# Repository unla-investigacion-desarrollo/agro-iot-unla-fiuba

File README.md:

# agro-iot-unla-fiuba

## Pasos necesarios para finalizar el proceso de subida.
1- Primero, para levantar el server de MQTT leer el readme dentro de /moquitto-docker
2- Luego, para levantar la capa lógica leer el readme dentro de /iot-src

## Nombre de aplicación que debe utilizarse.
sg.unla.edu.ar/iothuertas

## Persona a contactar como responsable de la aplicación.
Gustavo Hernan Siciliano (gussiciliano@gmail.com)

## Tiempo de vida de la aplicación en el servidor.
Todo 2024 (re evaluar en 2025)

## Extras (no necesarios para deployar en servidor):
a- Para cargar la placa con la configuración correcta del server MQTT leer el reame de /agroecologia-iot-dispositivo
b- Documentación de la placa:
https://drive.google.com/file/d/1S4R7Kyz0lglkcFME0CLmTT9d_WD0e9yo

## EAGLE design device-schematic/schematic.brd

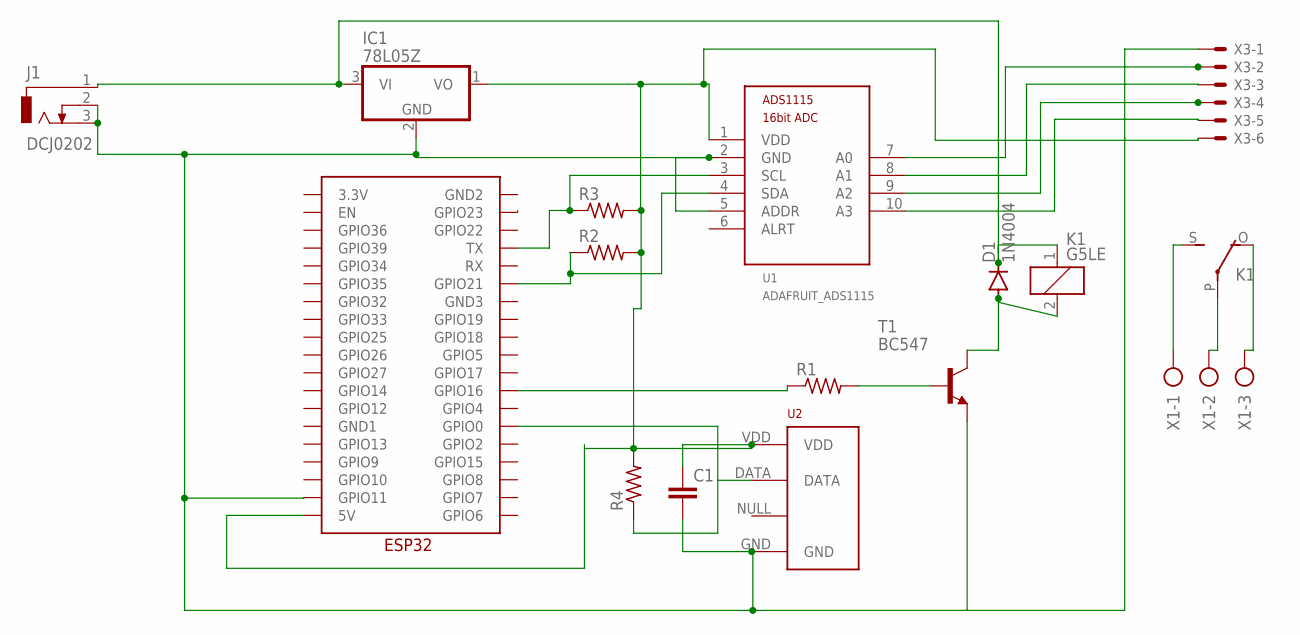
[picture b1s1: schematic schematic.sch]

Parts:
C1: C-EU025-025X050; C025-025X050
D1: 1N4004; DO41-10
IC1: 78L05Z; TO92
J1: DCJ0202
K1: G5LE
R1, R2, R3, R4: R-US_0309/12; 0309/12
T1: BC547; TO92
U1: ADAFRUIT_ADS1115; ADAFRUIT_ADS1115_16BIT_I2C_ADC
U2: RHT03_DHT-22_AM2302RA; RHT03_DHT-22/RA
U$1: ESP32_GRBL
X1: AK300/3
X3: KK-156-6

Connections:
unnamed: D1.A, K1.2, T1.3 (C)
unnamed: U1.10 (A3), X3.5
unnamed: R1.1, U$1.GPIO16
unnamed: R1.2, T1.2 (B)
unnamed: D1.C, IC1.3 (VI), J1.1, K1.1
unnamed: R3.1, U1.3 (SCL), U$1.TX
unnamed: R2.1, U1.4 (SDA), U$1.GPIO21
unnamed: R4.1, U2.DATA, U$1.GPIO0
unnamed: C1.2, IC1.2 (GND), J1.2, J1.3, T1.1 (E), U1.2 (GND), U1.5 (ADDR), U2.GND, U$1.GPIO11, X3.1
unnamed: K1.S, X1.1
unnamed: K1.P, X1.2
unnamed: K1.O, X1.3
unnamed: U1.8 (A1), X3.3
unnamed: C1.1, IC1.1 (VO), R2.2, R3.2, R4.2, U1.1 (VDD), U2.VDD, U$1.5V, X3.6
unnamed: U1.9 (A2), X3.4
unnamed: U1.7 (A0), X3.2

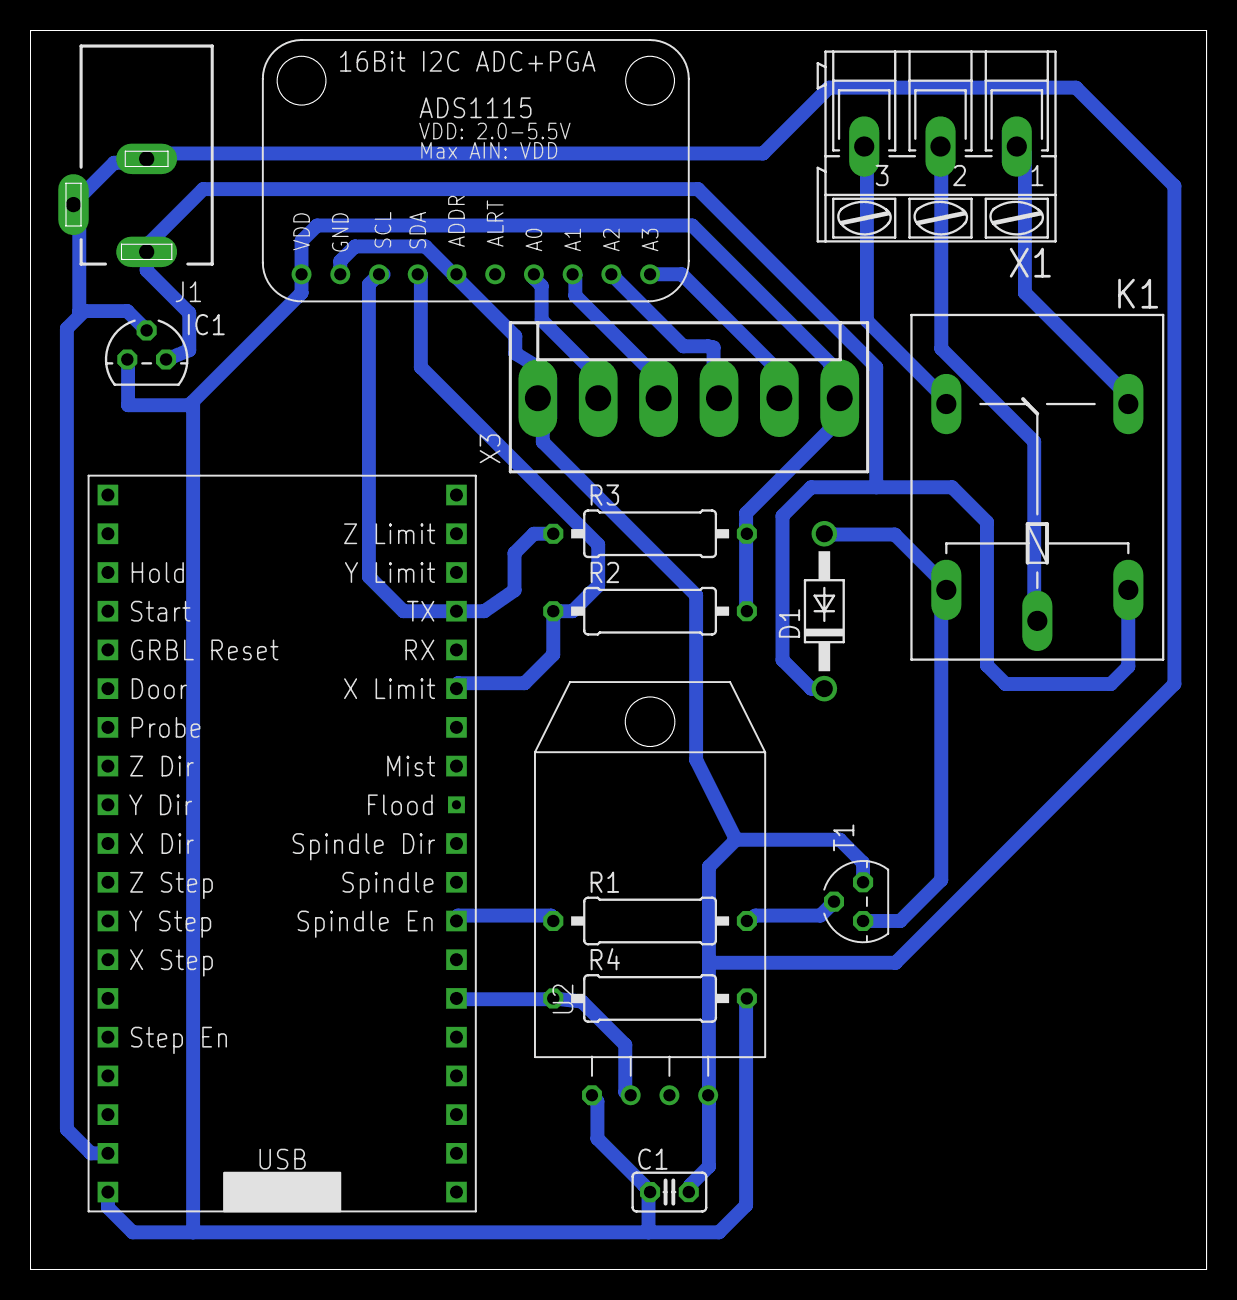
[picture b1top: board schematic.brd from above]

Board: 2 copper layers, 77.1 x 81.3 mm, 15 parts (0 on the bottom side), 16 nets.

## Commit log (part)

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2023-06-06 fist-structure
2023-06-11 done initial db and spring be
2023-06-12 adding simple transfer by mqtt
2023-06-12 done transfer but with errors
2023-06-12 done react docker integration
2023-06-14 wip-db
2023-06-16 fixes-mqtt-and-node
2023-06-16 insert-metrics-into-db
2023-06-16 fixes-fe-dash
2023-06-17 done-fixes
2023-06-19 adding auth and env vars
2023-06-19 fix-date-gmt
2023-06-21 adding subs and publish with config in C
2023-09-18 add json handler
2023-09-29 Funciones para guardar el array de sensores en memoria nvs
2023-10-04 fixes
2023-10-04 fixes for node Backend
2023-10-29 new port
2023-11-20 fixes for use diferent ports
2023-11-20 little fix
2023-11-20 fix node docker working with mysql
2023-11-20 final fixes
2023-11-20 fix-on-readme
2023-11-21 Automatic pin activation at 7 AM
2023-11-25 fixes for usar absolute path on react and spring
2023-11-25 fixes for use path on express and changer on readme
2023-11-28 hotfix-react-homepage
2025-09-20 v1.0.0 Major changes: accept different boards by centralizer_key, unify metrics received from the board, and update views.
2025-09-21 Se comenta creacion tabla sector_metric_acceptation_range
